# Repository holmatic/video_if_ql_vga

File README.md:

# **QLpicoVGA** - Video Interface QL-to-VGA with a Pi Pico 

This project creates the firmware for a DIY video interface based on the Rapsberry Pi Pico controller. It allows to connect a Sinclair QL computer to a standard VGA monitor.

One difficulty when using an old Sinclair QL nowadays is finding monitor that works well. The QL video output is a bit non-standard, many displays do not show the full 512 horizontal pixel, but instead crop the screen in some way.

This small Video-to VGA converter project is specially made for the QL signal and translates the 512x256 pixel screen to a standard pseudo-XGA resolution (1024x768 with a single QL pixel translating to a block of 2x3 XGA pixels). The Gold Standard for such a translation is the "QL-VGA" FPGA-based device by MarcelK. This project is a µC based C/C++ implementation, utilizing the highly configurable I/O of the RP2040 and its DMA capabilities for signal input and output. Phase and frequency detection and adjustment is done by the CPU on the fly utilizing fixed-point arithmetics.

- The VGA signal generation uses _MoeFH_'s simple but clever DMA-driven approach for the low-level part. Kudos to _MoeFH_!
- QL video signals are sampled at 32MS/s - with the QL Pixel clock running at 10MHz
- All timing parameters are specifically preset for the QL's video output, so the software will definitely not work well with any other video source, the project is not meant as a generic RGB-to-VGA converter.
- As a small diagnostic aid, the unavoidable "No Signal" bluescreen shows a simplified logic-analyzer type of graph for the input signals

## Hardware

This project is based on a Raspberry Pi Pico board and only needs a few additional components (resistors) for voltage level translation:

```
Controller Module: Raspberry Pi Pico 
```

## QL to Pico:

```
QL RGB                            Pi Pico
Connector                          Module

7 (QLRED)   ----[R 330 Ohm]----  GP3=Pin 5 ----[R 680 Ohm]---- GND 
6 (QLGREEN) ----[R 330 Ohm]----  GP5=Pin 7 ----[R 680 Ohm]---- GND
8 (QLBLUE)  ----[R 330 Ohm]----  GP7=Pin10 ----[R 680 Ohm]---- GND

4 (QLCSYNC) ----[R 100 Ohm]----  GP9=Pin12 ----[R 680 Ohm]---- GND

2 (QLGND)   -------------------  GND=Pin8

```

## Pico to VGA:

```
Pi Pico                          VGA
Module                        Connector

GP11=Pin15 ----[R 330 Ohm]----  1 (RED)
GP13=Pin17 ----[R 330 Ohm]----  2 (GREEN)
GP15=Pin20 ----[R 330 Ohm]----  3 (BLUE)

GP16=Pin21 ----[R 100 Ohm]---- 13 (HSYNC)
GP17=Pin22 ----[R 100 Ohm]---- 14 (VSYNC)

GND=Pin23  ------------------- 6,7,8,10,5 (GND)
```

Note: Place all resistors close to the Pi Pico module (<5cm) for best signal integrity.

## Power Supply Input

Raspberry Pi Pico needs a standard USB power suppy (needs <100mA, so no special requirements for the power supply). Some VGA monitors may even provide USB voltage via an integrated USB hub. 

## 1st Prototype

(Ehem - yes I know but it works ;-)	

# Loading the Firmware into the Pi Pico

Pi Pico operates like a USB memory stick when pushing the BOOTSEL button during while plugging into the USB port of a computer. Put the firmware "video_if_ql_vga.uf2" onto the drive. LED should show short flashes with a period of about 2 seconds. Please also refer to the Pi Pico documentation regarding firmware programming.

https://github.com/holmatic/video_if_ql_vga/releases

## PCB and 3D Printable Case

So [here](doc/pcb.md) for info on creating your own PCB and case

### Version Info

0.01 Initial version

0.05 Extend boot delay (startup fix for issue opbserved on some boards); minor adjustments to timing

---

Instruction v1.0

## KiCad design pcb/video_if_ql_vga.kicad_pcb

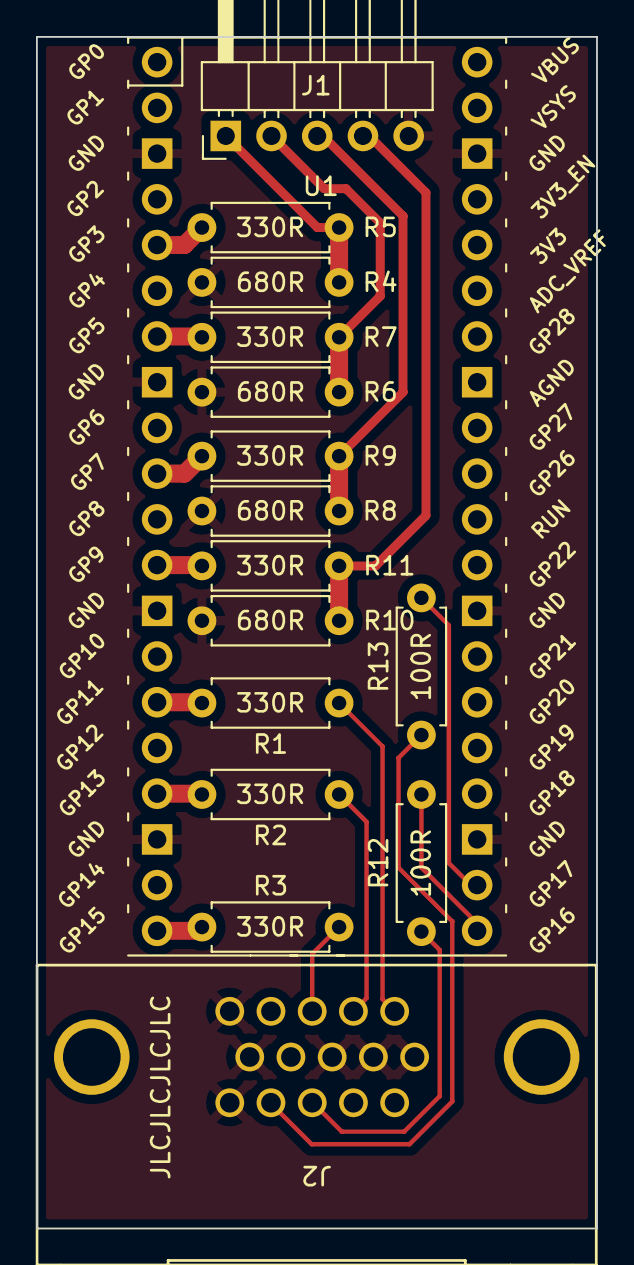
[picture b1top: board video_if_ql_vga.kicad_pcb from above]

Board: 2 copper layers, 31.1 x 66.2 mm, 16 parts (0 on the bottom side), 19 nets.

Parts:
J1: Conn_01x05; PinHeader_1x05_P2.54mm_Horizontal
J2: DB15_Female_HighDensity; CONN_L77HDE15SD1CH4FVGA_AMP
R1, R2, R3, R5, R7, R9, R11: 330R; R_Axial_DIN0207_L6.3mm_D2.5mm_P7.62mm_Horizontal
R4, R6, R8, R10: 680R; R_Axial_DIN0207_L6.3mm_D2.5mm_P7.62mm_Horizontal
R12, R13: 100R; R_Axial_DIN0207_L6.3mm_D2.5mm_P7.62mm_Horizontal
U1: SC0915; RPi_Pico_SMD_TH

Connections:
/BLUE: R3.1, U1.20 (GP15)
/GREEN: R2.1, U1.17 (GP13)
/HSYNC: R12.2, U1.21 (GP16)
/QLBLUE: R9.2, U1.10 (GP7)
/QLGREEN: R7.1, U1.7 (GP5)
/QLRED: R5.2, U1.5 (GP3)
/QLSYNC: R11.1, U1.12 (GP9)
/RED: R1.1, U1.15 (GP11)
/VSYNC: R13.2, U1.22 (GP17)
GND: J1.5, J2.5, J2.6, J2.7, J2.8, J2.10, J2.15, R4.1, R6.2, R8.1, R10.2, U1.3 (GND), U1.8 (GND), U1.13 (GND), U1.18 (GND), U1.23 (GND), U1.28 (GND), U1.38 (GND)
unnamed: J1.1, R4.2, R5.1
unnamed: J1.2, R6.1, R7.2
unnamed: J1.3, R8.2, R9.1
unnamed: J1.4, R10.1, R11.2
unnamed: J2.1, R1.2
unnamed: J2.2, R2.2
unnamed: J2.3, R3.2
unnamed: J2.13, R12.1
unnamed: J2.14, R13.1

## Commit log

2023-01-12 update documentation
2023-01-24 initial/experimental changes for Spectrum +2
2023-02-02 add support RP-2040-Zero layout
2023-02-02 update doc
2023-02-12 Initial PCB and Case designs
2023-02-18 experimentally use single-pin sync outputs for the PR2040 zero
2023-02-19 initial changes for existing layout
2023-03-05 Adjustments for phase locking with wider border
2023-03-05 Version 1.0 PCB assembled and tested
2023-03-05 Version update
2023-03-05 Extend start up delay to address boot issues on some boards (PR2040zero)
2024-07-01 Re-adjusted with longer cable
